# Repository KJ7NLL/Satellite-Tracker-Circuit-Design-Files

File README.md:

# Satellite-Tracker-Circuit-Design-Files
These are the files for the Desktop Satellite Tracker as well as the full size satellite tracker
The Rigid not flex files are for the full size tracker. They are the same as the Flex Board, but they are rigid instead of flexable. You will need wires to connect them.

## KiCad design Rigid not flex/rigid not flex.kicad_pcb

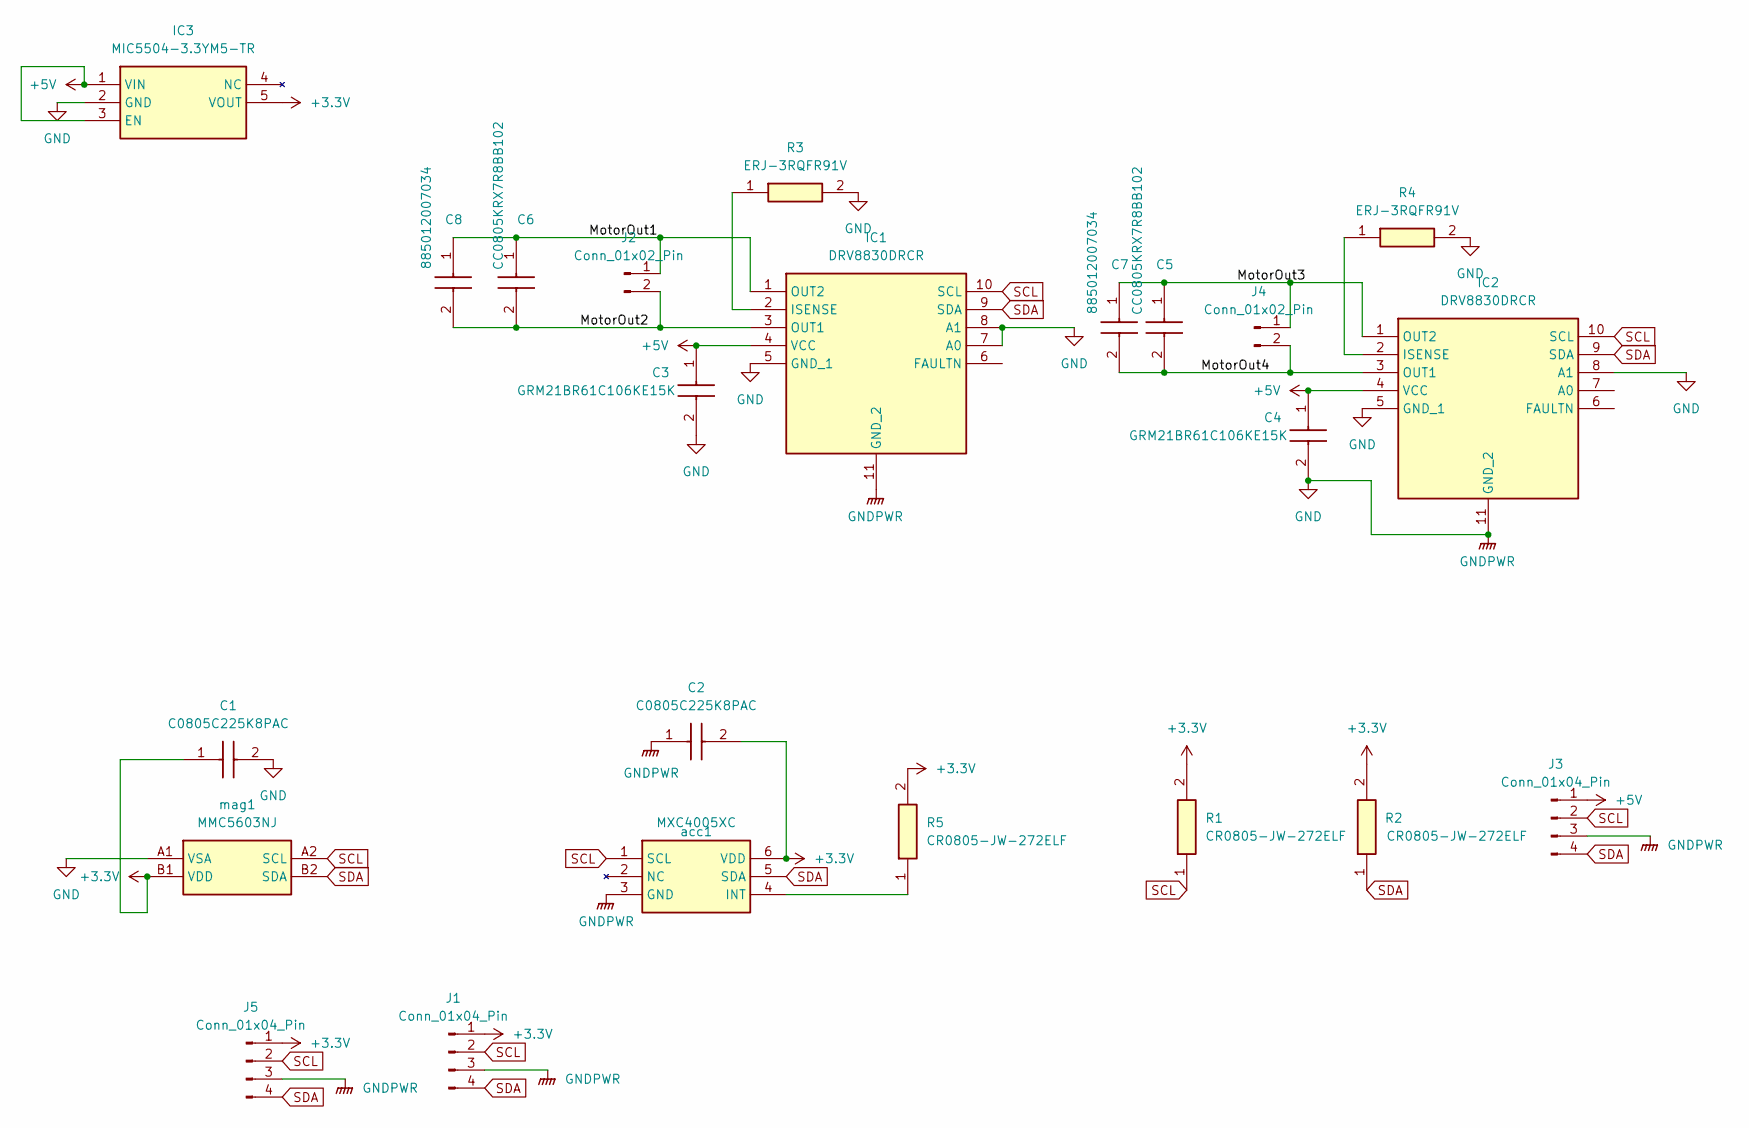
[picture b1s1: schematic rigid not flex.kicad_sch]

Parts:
C1, C2: C0805C225K8PAC; CAPC2012X140N; Mouser Part Number 80-C0805C225K8PAC
C3, C4: GRM21BR61C106KE15K; CAPC2012X145N; Mouser Part Number 81-GRM21BR61C106KE5K
C5, C6: CC0805KRX7R8BB102; CAPC2012X70N; Manufacturer_Part_Number CC0805KRX7R8BB102
C7, C8: 885012007034; CAPC2012X70N; Mouser Part Number 710-885012007034
IC1, IC2: DRV8830DRCR; SON50P300X300X100-11N-D; Mouser Part Number 595-DRV8830DRCR
IC3: MIC5504-3.3YM5-TR; SOT95P280X145-5N; Mouser Part Number 998-MIC5504-3.3YM5TR
J1, J3, J5: Conn_01x04_Pin; PinHeader_1x04_P2.54mm_Vertical
J2, J4: Conn_01x02_Pin; JST_XH_B2B-XH-A_1x02_P2.50mm_Vertical
R1, R2, R5: CR0805-JW-272ELF; RESC2012X60N; Mouser Part Number 652-CR0805JW-272ELF
R3, R4: ERJ-3RQFR91V; ERJ3_B_BQ_BW_LW_(0603); Mouser Part Number 667-ERJ-3RQFR91V
acc1: MXC4005XC; Mouser Part Number 438-MXC4005XC
mag1: MMC5603NJ; Mouser Part Number 438-MMC5603NJ

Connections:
+3.3V: C1.1, C2.2, IC3.5 (VOUT), J1.1, J5.1, R1.2, R2.2, R5.2, acc1.6 (VDD), mag1.B1 (VDD)
+5V: C3.1, C4.1, IC1.4 (VCC), IC2.4 (VCC), IC3.1 (VIN), IC3.3 (EN), J3.1
/MotorOut1: C6.1, C8.1, IC1.1 (OUT2), J2.1
/MotorOut2: C6.2, C8.2, IC1.3 (OUT1), J2.2
/MotorOut3: C5.1, C7.1, IC2.1 (OUT2), J4.1
/MotorOut4: C5.2, C7.2, IC2.3 (OUT1), J4.2
GND: C1.2, C2.1, C3.2, C4.2, IC1.5 (GND_1), IC1.7 (A0), IC1.8 (A1), IC1.11 (GND_2), IC2.5 (GND_1), IC2.8 (A1), IC2.11 (GND_2), IC3.2 (GND), J1.3, J3.3, J5.3, R3.2, R4.2, acc1.3 (GND), mag1.A1 (VSA)
unnamed: IC1.2 (ISENSE), R3.1
unnamed: IC2.2 (ISENSE), R4.1
unnamed: R5.1, acc1.4 (INT)
SCL: IC1.10 (SCL), IC2.10 (SCL), J1.2, J3.2, J5.2, R1.1, acc1.1 (SCL), mag1.A2 (SCL)
SDA: IC1.9 (SDA), IC2.9 (SDA), J1.4, J3.4, J5.4, R2.1, acc1.5 (SDA), mag1.B2 (SDA)

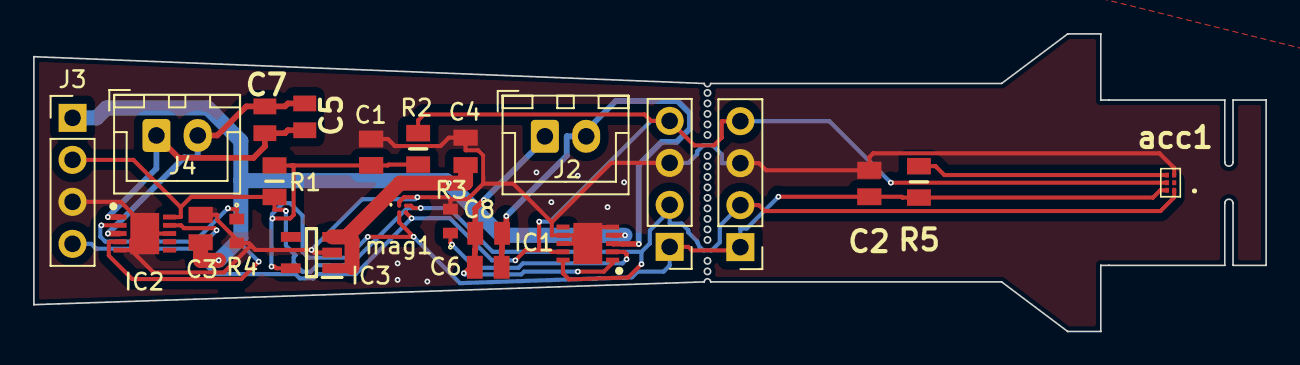
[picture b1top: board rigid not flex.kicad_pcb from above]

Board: 2 copper layers, 74.5 x 18.0 mm, 23 parts (0 on the bottom side), 12 nets.

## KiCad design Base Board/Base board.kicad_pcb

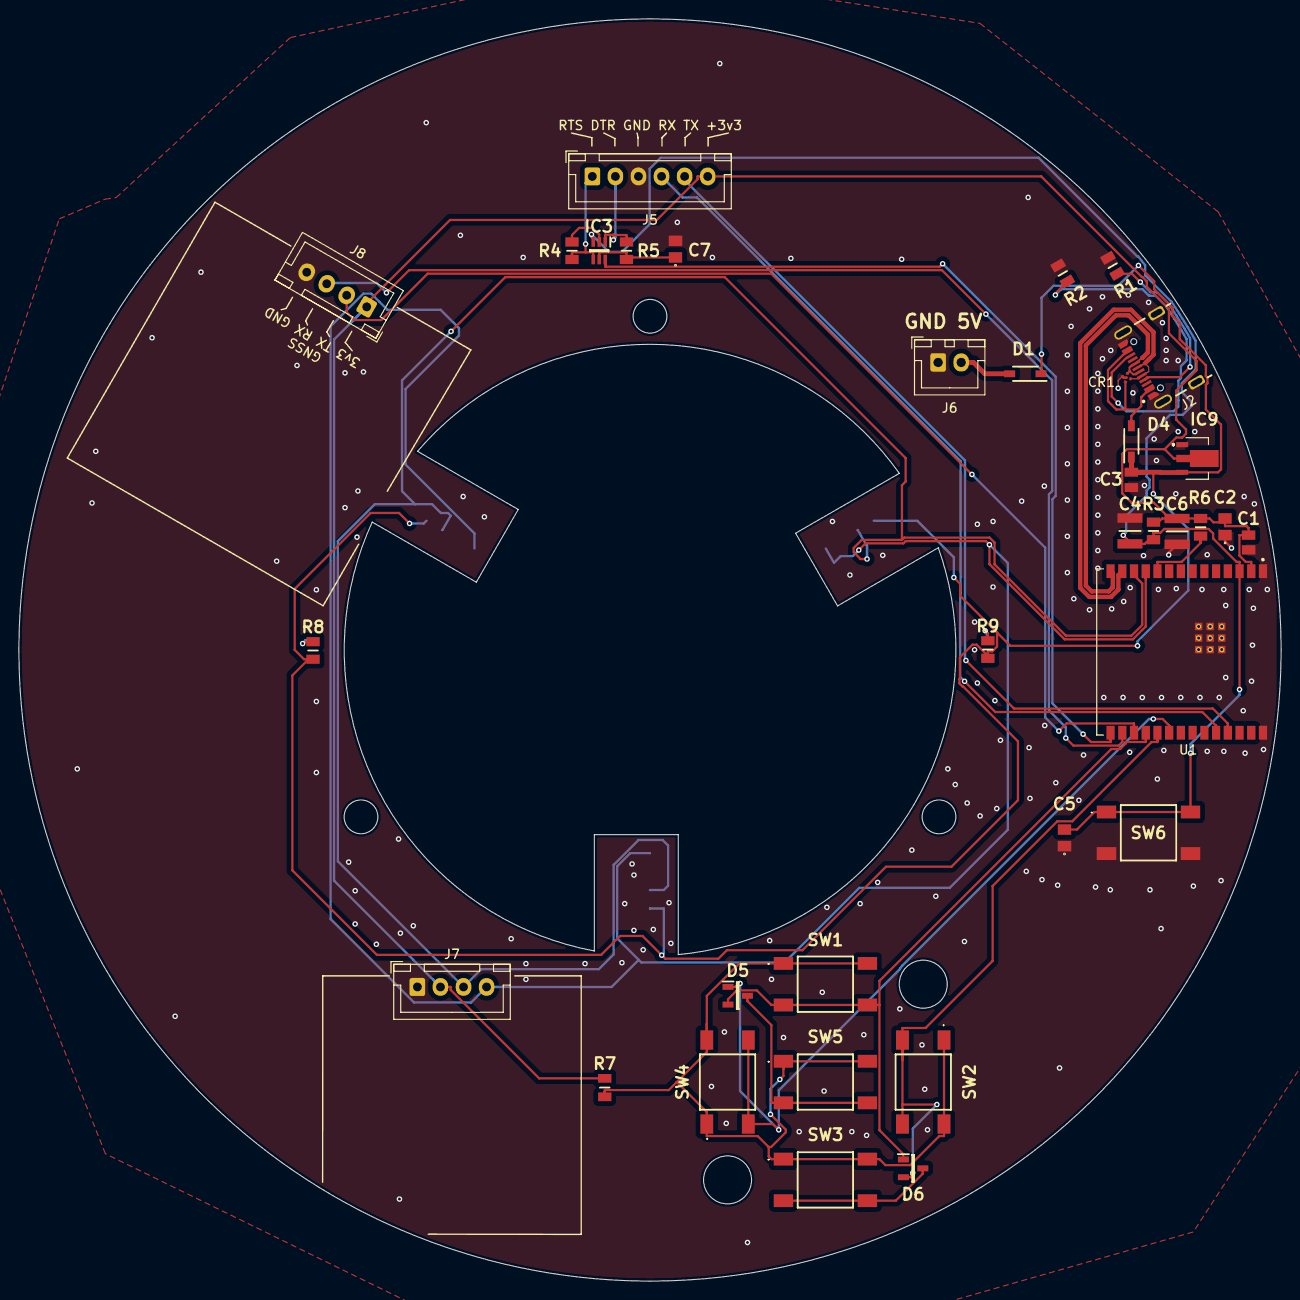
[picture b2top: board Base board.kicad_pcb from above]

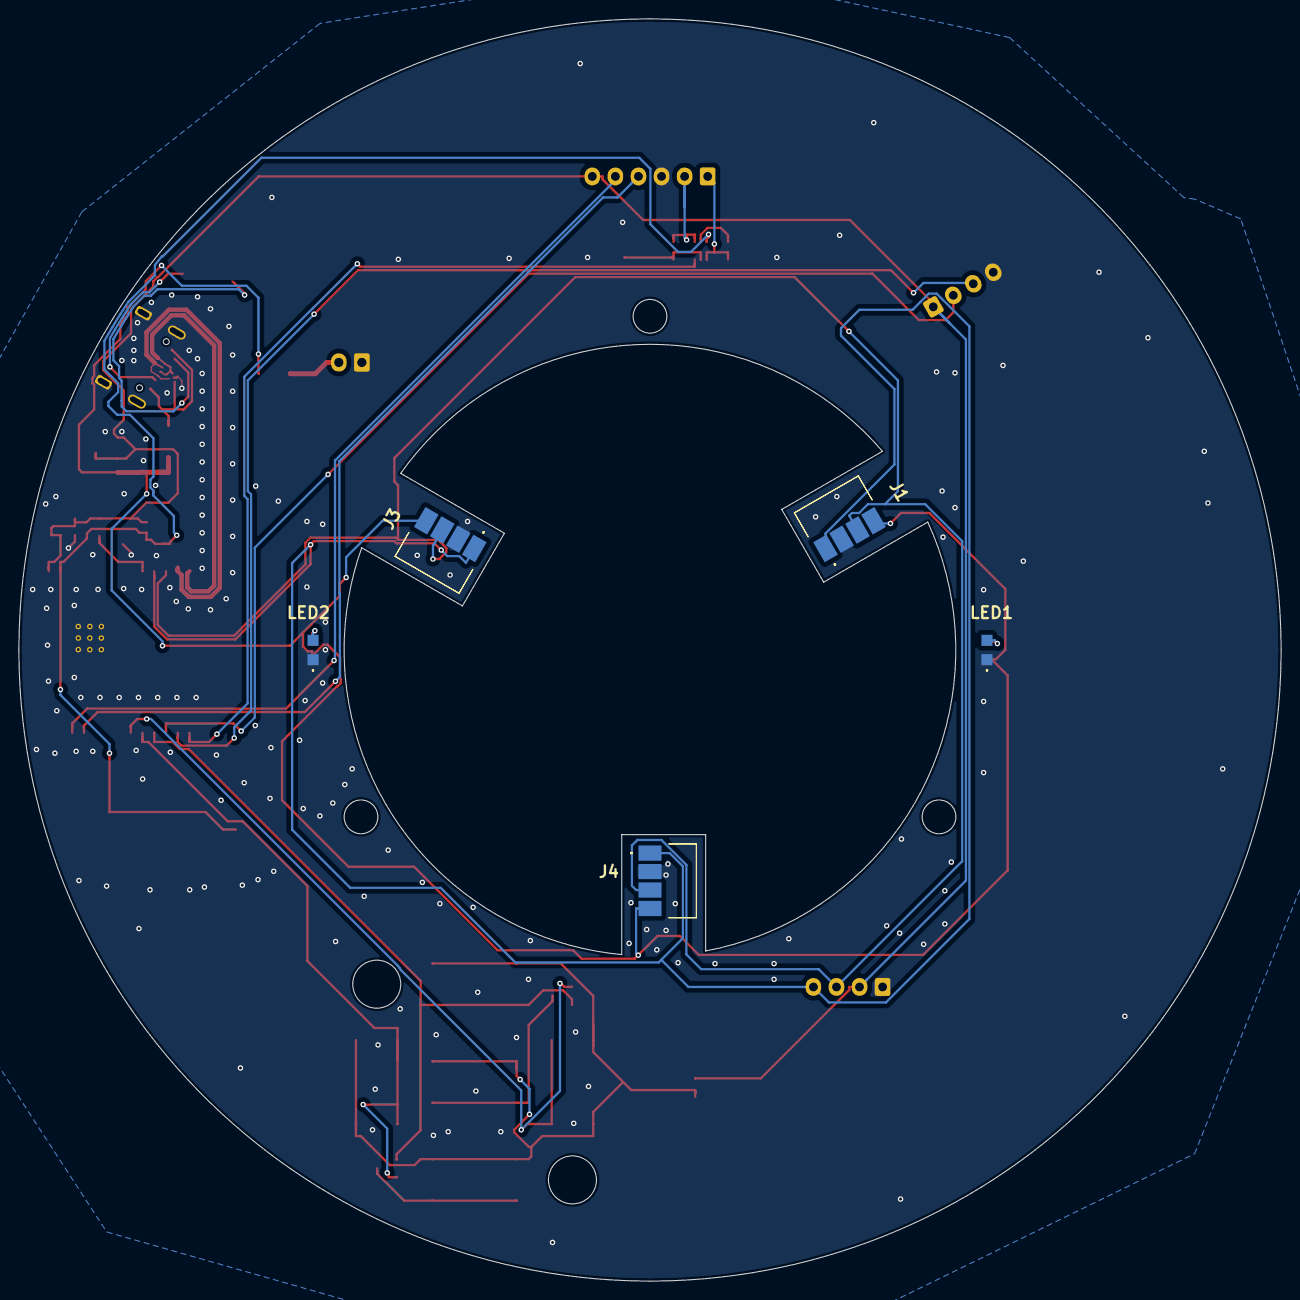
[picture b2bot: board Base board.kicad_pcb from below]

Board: 2 copper layers, 136.7 x 136.7 mm, 40 parts (5 on the bottom side), 30 nets.

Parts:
C1: CL21A226MQQNNNG; CAPC2012X140N
C2, C5, C7: C0805C104Z3VACTU; C0805
C3: GRM21BR61E106KA73K; CAPC2012X145N
C4, C6: C1210C476M9PAC; CAPC3225X280N
CR1: ESDAVLC5-4BX4; MICRO5_0P83X0P83X0P5_STM
D1, D4: 1N5819HW-7-F; SOD3716X145N
D5, D6: BAW56; SOT96P240X120-3N
IC3: BC847BDW1T1G; SOT65P210X110-6N
IC9: AZ1117CR-3.3TRG1; AZ1117CR33TRG1
J1, J3, J4: 47286-1001; 472861001
J2: USB4105-GF-A; USB4105-GF-A_GCT_USB4105-GF-A
J5: Conn_01x06_Pin; JST_XH_B6B-XH-A_1x06_P2.50mm_Vertical
J6: Conn_01x02_Pin; JST_XH_B2B-XH-A_1x02_P2.50mm_Vertical
J7, J8: Conn_01x04_Pin; JST_XH_B4B-XH-A_1x04_P2.50mm_Vertical
LED1, LED2: IN-S85AT5UW; INS85AT5UW
R1, R2: CRCW08055K10FKEA; RESC2012X50N
R3, R4, R5, R6: RK73H2ATTED1002F; RESC2012X60N
R7: CRCW08052K70JNEB; RESC2012X50N
R8, R9: CRG0805J470R; RESC2012X65N
SW1, SW2, SW3, SW4, SW5, SW6: TS04-66-43-BK-160-SMT; TS046643BK160SMT
U1: ESP32-C6-WROOM-1-N8; ESP32-C6-WROOM-1-N8_XCVR_ESP32-C6-WROOM-1-N8

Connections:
+3V3: C1.1, C2.2, C6.1, IC9.2 (OUTPUT), IC9.4 (VOUT), J5.6, J7.2, J8.1, R3.2, R6.2, R7.2, U1.2 (3V3)
+5V: C3.2, D1.1 (K), D4.1 (K), IC9.3 (INPUT), J1.4, J3.4, J4.4, R8.2, R9.2
CHIP_PU (3v3): C4.1, C5.2, IC3.3 (C1), R3.1, SW6.1 (NO_1), SW6.2 (NO_2), U1.3 (EN)
DTR: IC3.1 (E2), J5.2, R5.1
GND: C1.2, C2.1, C3.1, C4.2, C5.1, C6.2, C7.2, CR1.3 (I/O3), CR1.5 (GND), IC9.1 (ADJ/GND), J1.2, J2.A1_B12 (GND), J2.B1_A12 (GND), J2.SH1 (SHELL_GND), J2.SH2 (SHELL_GND), J2.SH3 (SHELL_GND), J2.SH4 (SHELL_GND), J3.2, J4.2, J5.3, J6.1, J7.1, J8.4, LED1.1 (K), LED2.1 (K), R1.2, R2.2, SW6.3 (COM_1), SW6.4 (COM_2), U1.1 (GND), U1.28 (GND), U1.29_1 (GND), U1.29_2 (GND), U1.29_3 (GND), U1.29_4 (GND), U1.29_5 (GND), U1.29_6 (GND), U1.29_7 (GND), U1.29_8 (GND), U1.29_9 (GND), U1.30 (GND)
GPIO9: IC3.6 (C2), U1.15 (IO9)
GPIO20: D5.2 (CATHODE_2), D6.1 (CATHODE_1), SW1.3 (COM_1), SW1.4 (COM_2), U1.18 (IO20)
GPIO21: D6.2 (CATHODE_2), SW2.3 (COM_1), SW2.4 (COM_2), U1.19 (IO21)
GPIO22: D5.1 (CATHODE_1), SW4.3 (COM_1), SW4.4 (COM_2), U1.20 (IO22)
unnamed: D1.2 (A), J6.2
unnamed: D5.3 (COMMON_ANODE), SW5.3 (COM_1), SW5.4 (COM_2)
unnamed: D6.3 (COMMON_ANODE), SW3.3 (COM_1), SW3.4 (COM_2)
unnamed: C7.1, IC3.5 (B1), R5.2
unnamed: IC3.2 (B2), R4.1
unnamed: J2.A5 (CC1), R1.1
unnamed: J2.B5 (CC2), R2.1
unnamed: J5.4, U1.24 (RXD0/GPIO17)
unnamed: J5.5, U1.25 (TXD0/GPIO16)
unnamed: J8.2, U1.17 (IO19)
unnamed: J8.3, U1.16 (IO18)
unnamed: LED1.2 (A), R8.1
unnamed: LED2.2 (A), R9.1
unnamed: R7.1, SW1.1 (NO_1), SW1.2 (NO_2), SW2.1 (NO_1), SW2.2 (NO_2), SW3.1 (NO_1), SW3.2 (NO_2), SW4.1 (NO_1), SW4.2 (NO_2), SW5.1 (NO_1), SW5.2 (NO_2)
unnamed: R6.1, U1.10 (IO8)
RTS: IC3.4 (E1), J5.1, R4.2
SCL: J1.3, J3.3, J4.3, J7.3, U1.12 (IO11)
SDA: J1.1, J3.1, J4.1, J7.4, U1.11 (IO10)
USB D+: CR1.4 (I/O4), J2.A6 (DP1), J2.B6 (DP2), U1.14 (IO13)
USB D-: CR1.1 (I/O1), J2.A7 (DN1), J2.B7 (DN2), U1.13 (IO12)
VBUS: CR1.2 (I/O2), D4.2 (A), J2.A4_B9 (VBUS), J2.B4_A9 (VBUS)

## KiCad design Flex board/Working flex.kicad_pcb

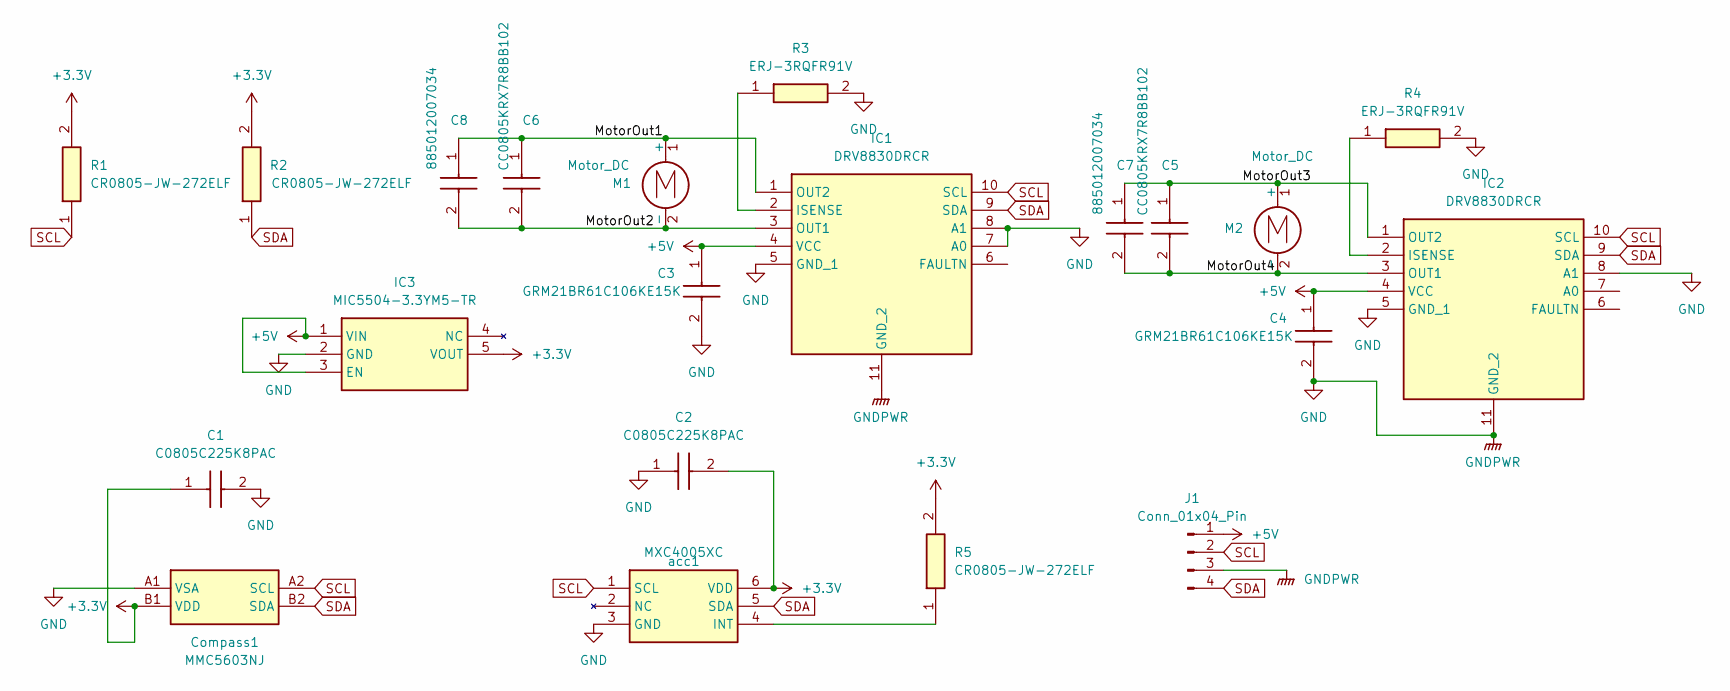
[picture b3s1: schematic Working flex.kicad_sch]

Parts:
C1, C2: C0805C225K8PAC; CAPC2012X140N; Mouser Part Number 80-C0805C225K8PAC
C3, C4: GRM21BR61C106KE15K; CAPC2012X145N; Mouser Part Number 81-GRM21BR61C106KE5K
C5, C6: CC0805KRX7R8BB102; CAPC2012X70N; Manufacturer_Part_Number CC0805KRX7R8BB102
C7, C8: 885012007034; CAPC2012X70N; Mouser Part Number 710-885012007034
Compass1: MMC5603NJ; Mouser Part Number 438-MMC5603NJ
IC1, IC2: DRV8830DRCR; SON50P300X300X100-11N-D; Mouser Part Number 595-DRV8830DRCR
IC3: MIC5504-3.3YM5-TR; SOT95P280X145-5N; Mouser Part Number 998-MIC5504-3.3YM5TR
J1: Conn_01x04_Pin; 4x 0.1 SMT pad
M1, M2: Motor_DC; Micro Motor
R1, R2, R5: CR0805-JW-272ELF; RESC2012X60N; Mouser Part Number 652-CR0805JW-272ELF
R3, R4: ERJ-3RQFR91V; ERJ3_B_BQ_BW_LW_(0603); Mouser Part Number 667-ERJ-3RQFR91V
acc1: MXC4005XC; Mouser Part Number 438-MXC4005XC

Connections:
+3.3V: C1.1, C2.2, Compass1.B1 (VDD), IC3.5 (VOUT), R1.2, R2.2, R5.2, acc1.6 (VDD)
+5V: C3.1, C4.1, IC1.4 (VCC), IC2.4 (VCC), IC3.1 (VIN), IC3.3 (EN), J1.1
/MotorOut1: C6.1, C8.1, IC1.1 (OUT2), M1.1 (+)
/MotorOut2: C6.2, C8.2, IC1.3 (OUT1), M1.2 (-)
/MotorOut3: C5.1, C7.1, IC2.1 (OUT2), M2.1 (+)
/MotorOut4: C5.2, C7.2, IC2.3 (OUT1), M2.2 (-)
GND: C1.2, C2.1, C3.2, C4.2, Compass1.A1 (VSA), IC1.5 (GND_1), IC1.7 (A0), IC1.8 (A1), IC1.11 (GND_2), IC2.5 (GND_1), IC2.8 (A1), IC2.11 (GND_2), IC3.2 (GND), J1.3, R3.2, R4.2, acc1.3 (GND)
unnamed: IC1.2 (ISENSE), R3.1
unnamed: IC2.2 (ISENSE), R4.1
unnamed: R5.1, acc1.4 (INT)
SCL: Compass1.A2 (SCL), IC1.10 (SCL), IC2.10 (SCL), J1.2, R1.1, acc1.1 (SCL)
SDA: Compass1.B2 (SDA), IC1.9 (SDA), IC2.9 (SDA), J1.4, R2.1, acc1.5 (SDA)

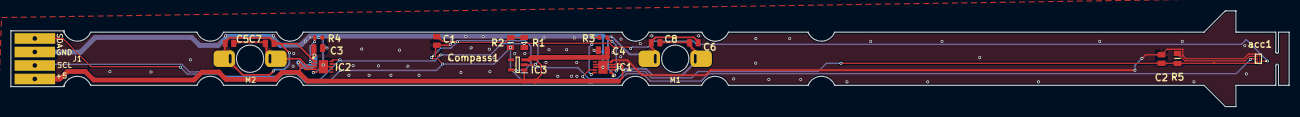
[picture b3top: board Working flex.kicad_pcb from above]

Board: 2 copper layers, 240.5 x 18.0 mm, 21 parts (0 on the bottom side), 12 nets.

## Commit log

2025-03-30 Added circuit design files
